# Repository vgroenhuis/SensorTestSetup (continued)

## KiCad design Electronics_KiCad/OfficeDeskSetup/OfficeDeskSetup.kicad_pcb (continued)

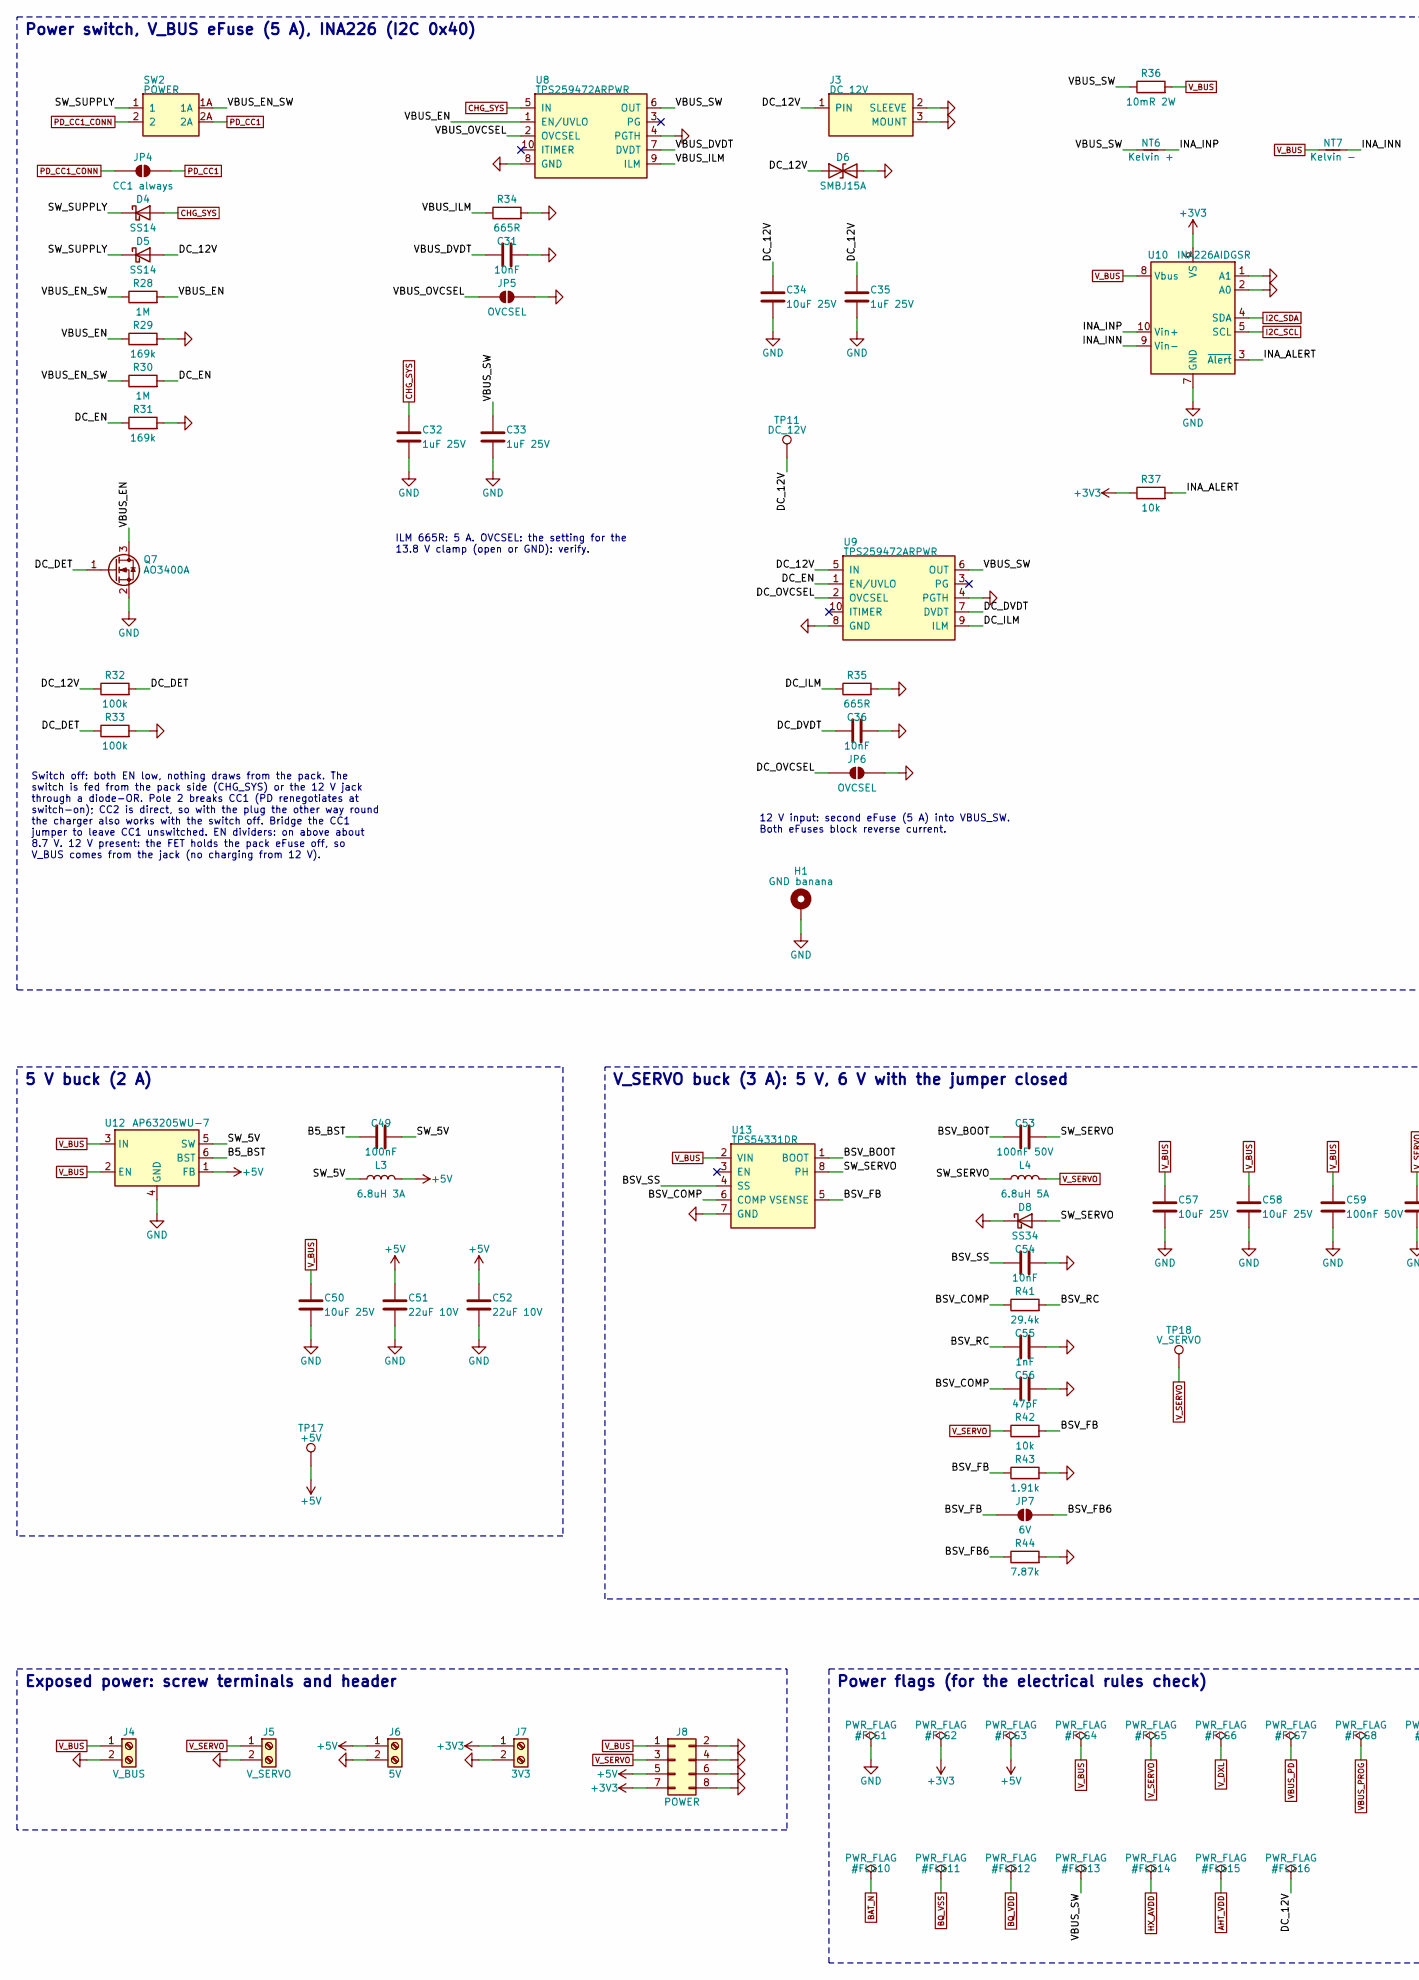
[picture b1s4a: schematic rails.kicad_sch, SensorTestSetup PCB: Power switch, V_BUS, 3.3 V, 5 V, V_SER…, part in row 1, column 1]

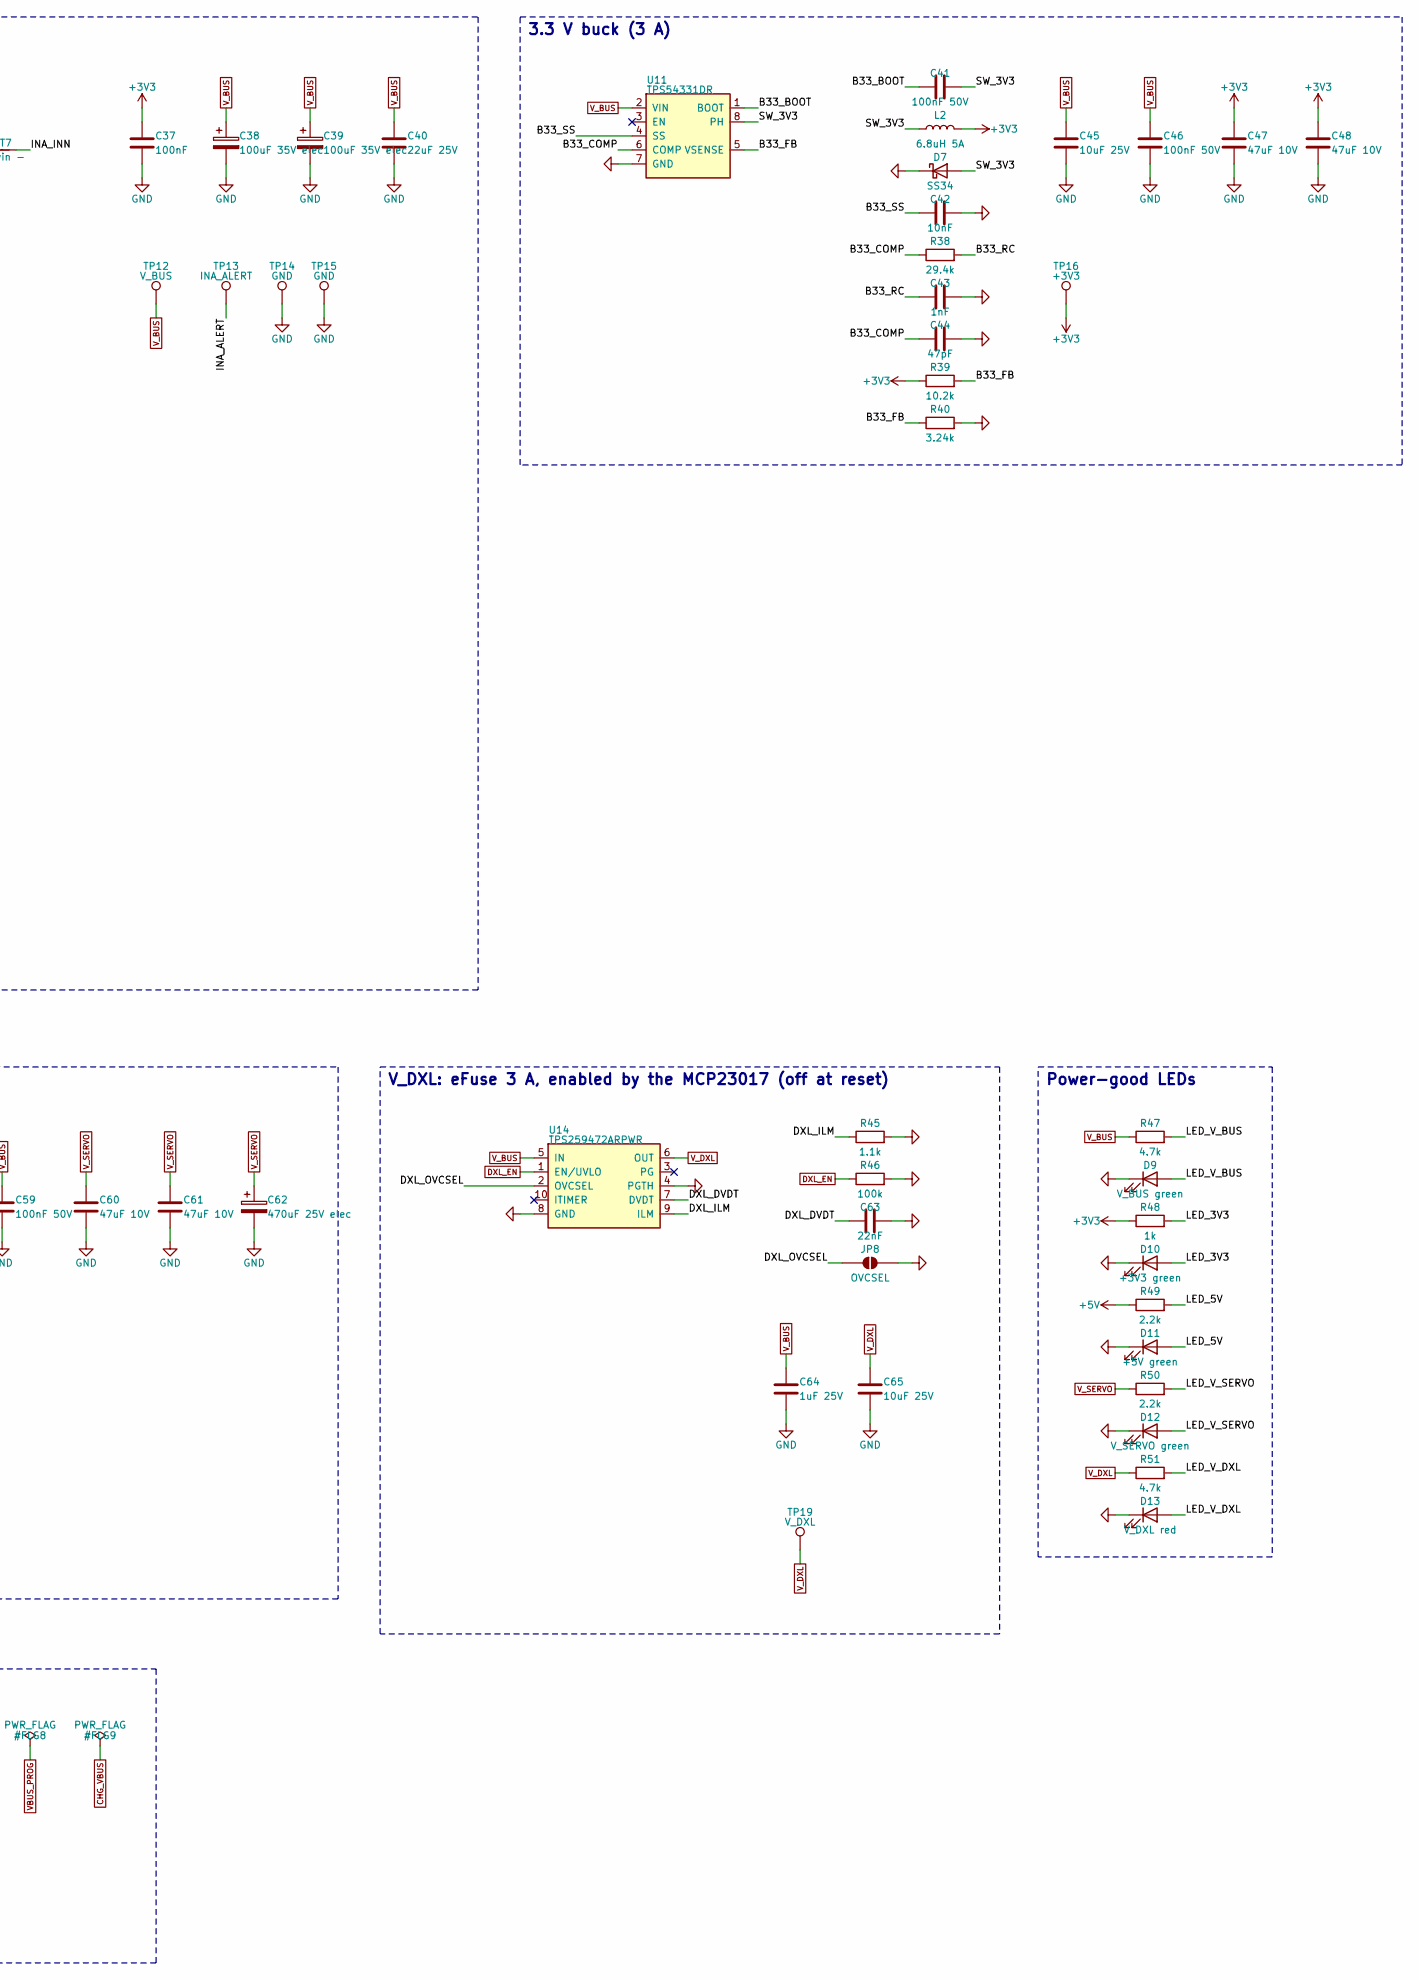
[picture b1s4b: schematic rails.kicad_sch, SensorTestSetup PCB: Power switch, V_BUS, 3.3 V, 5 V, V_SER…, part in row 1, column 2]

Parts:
C31, C36, C42, C54: 10nF; C_0603_1608Metric; LCSC C57112
C32, C33, C35, C64: 1uF 25V; C_0603_1608Metric; LCSC C15849
C34, C45, C50, C57, C58, C65: 10uF 25V; C_1206_3216Metric; LCSC C13585
C37, C49: 100nF; C_0603_1608Metric; LCSC C14663
C38, C39: 100uF 35V elec; CP_Elec_8x10; LCSC C2895269
C40: 22uF 25V; C_1206_3216Metric; LCSC C12891
C41, C46, C53, C59: 100nF 50V; C_0603_1608Metric; LCSC C14663
C43, C55: 1nF; C_0603_1608Metric; LCSC C1588
C44, C56: 47pF; C_0603_1608Metric; LCSC C1671
C47, C48, C60, C61: 47uF 10V; C_1206_3216Metric; LCSC C96123
C51, C52: 22uF 10V; C_1206_3216Metric; LCSC C12891
C62: 470uF 25V elec; CP_Elec_10x10; LCSC C3445246
C63: 22nF; C_0603_1608Metric; LCSC C21122
D4, D5: SS14; D_SMA; LCSC C2480
D6: SMBJ15A; D_SMB; LCSC C435932
D7, D8: SS34; D_SMA; LCSC C8678
D9: V_BUS green; LED_0603_1608Metric; LCSC C12624
D10: +3V3 green; LED_0603_1608Metric; LCSC C12624
D11: +5V green; LED_0603_1608Metric; LCSC C12624
D12: V_SERVO green; LED_0603_1608Metric; LCSC C12624
D13: V_DXL red; LED_0603_1608Metric; LCSC C2286
H1: GND banana; BananaHole_4.1mm_Pad
J3: DC 12V; DC-IN-TH_HX-DC007B-2.5; LCSC C17701683
J4: V_BUS; TerminalBlock_Phoenix_MKDS-1,5-2-5.08_1x02_P5.08mm_Horizont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; LCSC C8465
J5: V_SERVO; TerminalBlock_Phoenix_MKDS-1,5-2-5.08_1x02_P5.08mm_Horizont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; LCSC C8465
J6: 5V; TerminalBlock_Phoenix_MKDS-1,5-2-5.08_1x02_P5.08mm_Horizont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; LCSC C8465
J7: 3V3; TerminalBlock_Phoenix_MKDS-1,5-2-5.08_1x02_P5.08mm_Horizont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; LCSC C8465
J8: POWER; PinHeader_2x04_P2.54mm_Vertical; LCSC C32713277
JP4: CC1 always; SolderJumper-2_P1.3mm_Open_RoundedPad1.0x1.5mm
JP5, JP6, JP8: OVCSEL; SolderJumper-2_P1.3mm_Open_RoundedPad1.0x1.5mm
JP7: 6V; SolderJumper-2_P1.3mm_Open_RoundedPad1.0x1.5mm
L2, L4: 6.8uH 5A; IND-SMD_L7.0-W6.6; LCSC C167221
L3: 6.8uH 3A; IND-SMD_L7.0-W6.6; LCSC C167221
NT6: Kelvin +; NetTie-2_SMD_Pad0.5mm
NT7: Kelvin -; NetTie-2_SMD_Pad0.5mm
Q7: AO3400A; SOT-23; LCSC C20917
R28, R30: 1M; R_0603_1608Metric; LCSC C22935
R29, R31: 169k; R_0603_1608Metric; LCSC C22817
R32, R33, R46: 100k; R_0603_1608Metric; LCSC C25803
R34, R35: 665R; R_0603_1608Metric; LCSC C218112
R36: 10mR 2W; R_2512_6332Metric; LCSC C192580
R37, R42: 10k; R_0603_1608Metric; LCSC C25804
R38, R41: 29.4k; R_0603_1608Metric; LCSC C22974
R39: 10.2k; R_0603_1608Metric; LCSC C22772
R40: 3.24k; R_0603_1608Metric; LCSC C22994
R43: 1.91k; R_0603_1608Metric; LCSC C22853
R44: 7.87k; R_0603_1608Metric; LCSC C23236
R45: 1.1k; R_0603_1608Metric; LCSC C22764
R47, R51: 4.7k; R_0603_1608Metric; LCSC C23162
R48: 1k; R_0603_1608Metric; LCSC C21190
R49, R50: 2.2k; R_0603_1608Metric; LCSC C4190
SW2: POWER; SW-TH_SS21-BBIWG2-B; LCSC C6775929
TP11: DC_12V; TestPoint_Pad_D1.5mm
TP12: V_BUS; TestPoint_Pad_D1.5mm
TP13: INA_ALERT; TestPoint_Pad_D1.5mm
TP14, TP15: GND; TestPoint_Pad_D1.5mm
TP16: +3V3; TestPoint_Pad_D1.5mm
TP17: +5V; TestPoint_Pad_D1.5mm
TP18: V_SERVO; TestPoint_Pad_D1.5mm
TP19: V_DXL; TestPoint_Pad_D1.5mm
U8, U9, U14: TPS259472ARPWR; VQFN-10_L2.0-W2.0-P0.45-TL; LCSC C3662789
U10: INA226AIDGSR; TSSOP-10_3x3mm_P0.5mm; LCSC C49851
U11, U13: TPS54331DR; SOIC-8_3.9x4.9mm_P1.27mm; LCSC C9865
U12: AP63205WU-7; TSOT-23-6; LCSC C2071056

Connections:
+3V3: C37.1, C47.1, C48.1, J7.1, J8.7, L2.2, R37.1, R39.1, R48.1, TP16.1, U10.6 (VS); also elsewhere on the board
+5V: C51.1, C52.1, J6.1, J8.5, L3.2, R49.1, TP17.1, U12.1 (FB); also elsewhere on the board
/3 Power switch, V_BUS, 3.3 V, 5 V, V_SERVO, V_DXL/B5_BST: C49.1, U12.6 (BST)
/3 Power switch, V_BUS, 3.3 V, 5 V, V_SERVO, V_DXL/B33_BOOT: C41.1, U11.1 (BOOT)
/3 Power switch, V_BUS, 3.3 V, 5 V, V_SERVO, V_DXL/B33_COMP: C44.1, R38.1, U11.6 (COMP)
/3 Power switch, V_BUS, 3.3 V, 5 V, V_SERVO, V_DXL/B33_FB: R39.2, R40.1, U11.5 (VSENSE)
/3 Power switch, V_BUS, 3.3 V, 5 V, V_SERVO, V_DXL/B33_RC: C43.1, R38.2
/3 Power switch, V_BUS, 3.3 V, 5 V, V_SERVO, V_DXL/B33_SS: C42.1, U11.4 (SS)
/3 Power switch, V_BUS, 3.3 V, 5 V, V_SERVO, V_DXL/BSV_BOOT: C53.1, U13.1 (BOOT)
/3 Power switch, V_BUS, 3.3 V, 5 V, V_SERVO, V_DXL/BSV_COMP: C56.1, R41.1, U13.6 (COMP)
/3 Power switch, V_BUS, 3.3 V, 5 V, V_SERVO, V_DXL/BSV_FB: JP7.1 (A), R42.2, R43.1, U13.5 (VSENSE)
/3 Power switch, V_BUS, 3.3 V, 5 V, V_SERVO, V_DXL/BSV_FB6: JP7.2 (B), R44.1
/3 Power switch, V_BUS, 3.3 V, 5 V, V_SERVO, V_DXL/BSV_RC: C55.1, R41.2
/3 Power switch, V_BUS, 3.3 V, 5 V, V_SERVO, V_DXL/BSV_SS: C54.1, U13.4 (SS)
/3 Power switch, V_BUS, 3.3 V, 5 V, V_SERVO, V_DXL/DC_12V: C34.1, C35.1, D5.2 (A), D6.1 (A1), J3.1 (PIN), R32.1, TP11.1, U9.5 (IN)
/3 Power switch, V_BUS, 3.3 V, 5 V, V_SERVO, V_DXL/DC_DET: Q7.1 (G), R32.2, R33.1
/3 Power switch, V_BUS, 3.3 V, 5 V, V_SERVO, V_DXL/DC_DVDT: C36.1, U9.7 (DVDT)
/3 Power switch, V_BUS, 3.3 V, 5 V, V_SERVO, V_DXL/DC_EN: R30.2, R31.1, U9.1 (EN/UVLO)
/3 Power switch, V_BUS, 3.3 V, 5 V, V_SERVO, V_DXL/DC_ILM: R35.1, U9.9 (ILM)
/3 Power switch, V_BUS, 3.3 V, 5 V, V_SERVO, V_DXL/DC_OVCSEL: JP6.1 (A), U9.2 (OVCSEL)
/3 Power switch, V_BUS, 3.3 V, 5 V, V_SERVO, V_DXL/DXL_DVDT: C63.1, U14.7 (DVDT)
/3 Power switch, V_BUS, 3.3 V, 5 V, V_SERVO, V_DXL/DXL_ILM: R45.1, U14.9 (ILM)
/3 Power switch, V_BUS, 3.3 V, 5 V, V_SERVO, V_DXL/DXL_OVCSEL: JP8.1 (A), U14.2 (OVCSEL)
/3 Power switch, V_BUS, 3.3 V, 5 V, V_SERVO, V_DXL/INA_ALERT: R37.2, TP13.1, U10.3 (~Alert)
/3 Power switch, V_BUS, 3.3 V, 5 V, V_SERVO, V_DXL/INA_INN: NT7.2, U10.9 (Vin-)
/3 Power switch, V_BUS, 3.3 V, 5 V, V_SERVO, V_DXL/INA_INP: NT6.2, U10.10 (Vin+)
/3 Power switch, V_BUS, 3.3 V, 5 V, V_SERVO, V_DXL/LED_3V3: D10.2 (A), R48.2
/3 Power switch, V_BUS, 3.3 V, 5 V, V_SERVO, V_DXL/LED_5V: D11.2 (A), R49.2
/3 Power switch, V_BUS, 3.3 V, 5 V, V_SERVO, V_DXL/LED_V_BUS: D9.2 (A), R47.2
/3 Power switch, V_BUS, 3.3 V, 5 V, V_SERVO, V_DXL/LED_V_DXL: D13.2 (A), R51.2
/3 Power switch, V_BUS, 3.3 V, 5 V, V_SERVO, V_DXL/LED_V_SERVO: D12.2 (A), R50.2
/3 Power switch, V_BUS, 3.3 V, 5 V, V_SERVO, V_DXL/SW_3V3: C41.2, D7.2 (A), L2.1, U11.8 (PH)
/3 Power switch, V_BUS, 3.3 V, 5 V, V_SERVO, V_DXL/SW_5V: C49.2, L3.1, U12.5 (SW)
/3 Power switch, V_BUS, 3.3 V, 5 V, V_SERVO, V_DXL/SW_SERVO: C53.2, D8.2 (A), L4.1, U13.8 (PH)
/3 Power switch, V_BUS, 3.3 V, 5 V, V_SERVO, V_DXL/SW_SUPPLY: D4.1 (K), D5.1 (K), SW2.1
/3 Power switch, V_BUS, 3.3 V, 5 V, V_SERVO, V_DXL/VBUS_DVDT: C31.1, U8.7 (DVDT)
/3 Power switch, V_BUS, 3.3 V, 5 V, V_SERVO, V_DXL/VBUS_EN: Q7.3 (D), R28.2, R29.1, U8.1 (EN/UVLO)
/3 Power switch, V_BUS, 3.3 V, 5 V, V_SERVO, V_DXL/VBUS_EN_SW: R28.1, R30.1, SW2.1A
/3 Power switch, V_BUS, 3.3 V, 5 V, V_SERVO, V_DXL/VBUS_ILM: R34.1, U8.9 (ILM)
/3 Power switch, V_BUS, 3.3 V, 5 V, V_SERVO, V_DXL/VBUS_OVCSEL: JP5.1 (A), U8.2 (OVCSEL)
/3 Power switch, V_BUS, 3.3 V, 5 V, V_SERVO, V_DXL/VBUS_SW: C33.1, NT6.1, R36.1, U8.6 (OUT), U9.6 (OUT)
CHG_SYS: C32.1, D4.2 (A), U8.5 (IN); also elsewhere on the board
DXL_EN: R46.1, U14.1 (EN/UVLO); also elsewhere on the board
GND: C31.2, C32.2, C33.2, C34.2, C35.2, C36.2, C37.2, C38.2, C39.2, C40.2, C42.2, C43.2, C44.2, C45.2, C46.2, C47.2, C48.2, C50.2, C51.2, C52.2, C54.2, C55.2, C56.2, C57.2, C58.2, C59.2, C60.2, C61.2, C62.2, C63.2, C64.2, C65.2, D6.2 (A2), D7.1 (K), D8.1 (K), D9.1 (K), D10.1 (K), D11.1 (K), D12.1 (K), D13.1 (K), H1.1, J3.2 (SLEEVE), J3.3 (MOUNT), J4.2, J5.2, J6.2, J7.2, J8.2, J8.4, J8.6, J8.8, JP5.2 (B), JP6.2 (B), JP8.2 (B), Q7.2 (S), R29.2, R31.2, R33.2, R34.2, R35.2, R40.2, R43.2, R44.2, R45.2, R46.2, TP14.1, TP15.1, U8.4 (PGTH), U8.8 (GND), U9.4 (PGTH), U9.8 (GND), U10.1 (A1), U10.2 (A0), U10.7 (GND), U11.7 (GND), U12.4 (GND), U13.7 (GND), U14.4 (PGTH), U14.8 (GND); also elsewhere on the board
I2C_SCL: U10.5 (SCL); also elsewhere on the board
I2C_SDA: U10.4 (SDA); also elsewhere on the board
PD_CC1: JP4.2 (B), SW2.2A; also elsewhere on the board
PD_CC1_CONN: JP4.1 (A), SW2.2; also elsewhere on the board
V_BUS: C38.1, C39.1, C40.1, C45.1, C46.1, C50.1, C57.1, C58.1, C59.1, C64.1, J4.1, J8.1, NT7.1, R36.2, R47.1, TP12.1, U10.8 (Vbus), U11.2 (VIN), U12.2 (EN), U12.3 (IN), U13.2 (VIN), U14.5 (IN); also elsewhere on the board
V_DXL: C65.1, R51.1, TP19.1, U14.6 (OUT); also elsewhere on the board
V_SERVO: C60.1, C61.1, C62.1, J5.1, J8.3, L4.2, R42.1, R50.1, TP18.1; also elsewhere on the board

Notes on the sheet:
Switch off: both EN low, nothing draws from the pack. The switch is fed from the pack side (CHG_SYS) or the 12 V jack through a diode-OR. Pole 2 breaks CC1 (PD renegotiates at switch-on); CC2 is direct, so with the plug the other way round the charger also works with the switch off. Bridge the CC1 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
ILM 665R: 5 A. OVCSEL: the setting for the 13.8 V clamp (open or GND): verify.
12 V input: second eFuse (5 A) into VBUS_SW. Both eFuses block reverse current.
Power switch, V_BUS eFuse (5 A), INA226 (I2C 0x40)
3.3 V buck (3 A)
5 V buck (2 A)
V_SERVO buck (3 A): 5 V, 6 V with the jumper closed
V_DXL: eFuse 3 A, enabled by the MCP23017 (off at reset)
Power-good LEDs
Exposed power: screw terminals and header
Power flags (for the electrical rules check)

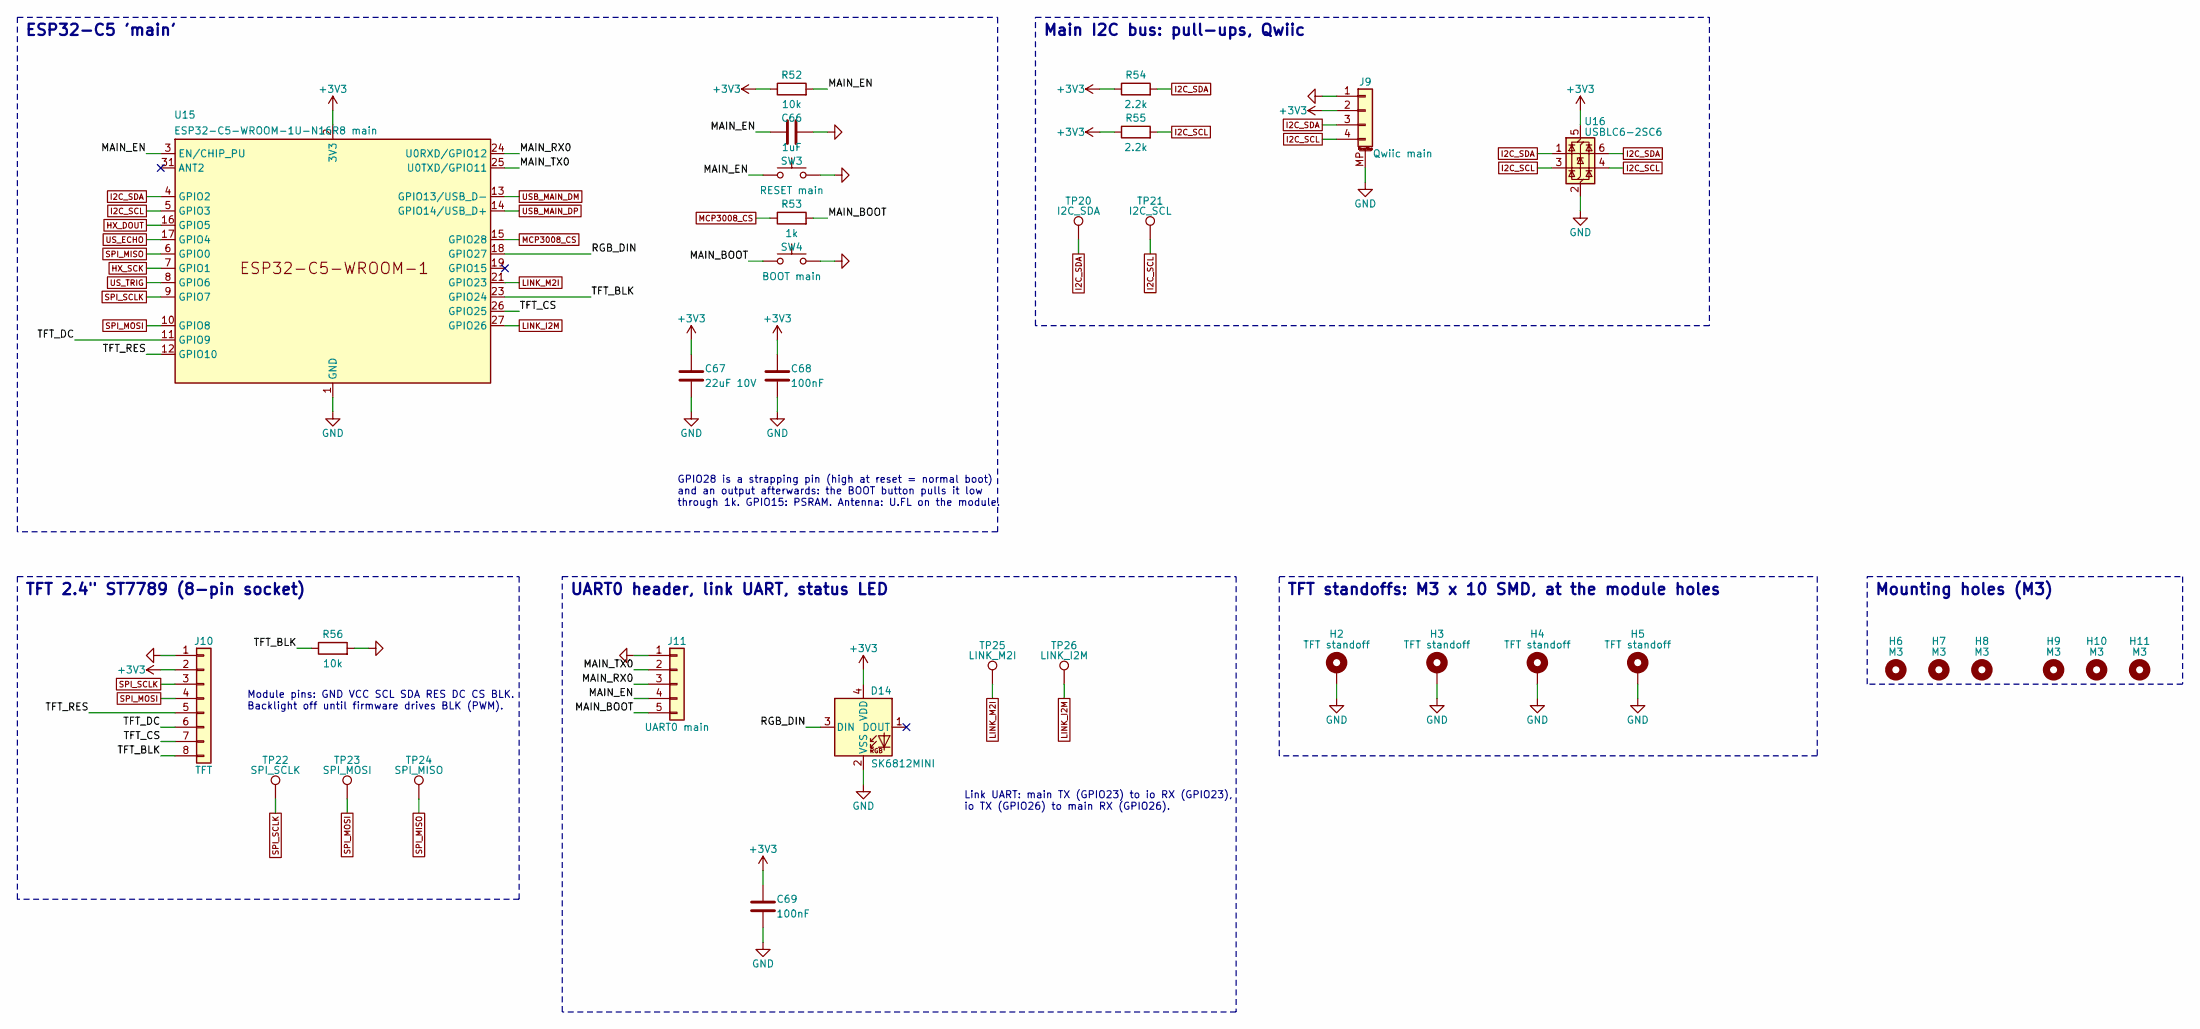
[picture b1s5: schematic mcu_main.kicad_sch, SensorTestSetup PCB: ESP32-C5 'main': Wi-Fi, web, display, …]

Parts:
C66: 1uF; C_0603_1608Metric; LCSC C15849
C67: 22uF 10V; C_1206_3216Metric; LCSC C12891
C68, C69: 100nF; C_0603_1608Metric; LCSC C14663
D14: SK6812MINI; LED_SK6812MINI_PLCC4_3.5x3.5mm_P1.75mm; LCSC C5183448
H2, H3, H4, H5: TFT standoff; SCREW-SMD_BD5.6-D4.1-H10; LCSC C2916370
H6, H7, H8, H9, H10, H11: M3; MountingHole_3.2mm_M3
J9: Qwiic main; JST_SH_SM04B-SRSS-TB_1x04-1MP_P1.00mm_Horizontal; LCSC C51940130
J10: TFT; PinSocket_1x08_P2.54mm_Vertical; LCSC C27438
J11: UART0 main; PinHeader_1x05_P2.54mm_Vertical; LCSC C32713271
R52, R56: 10k; R_0603_1608Metric; LCSC C25804
R53: 1k; R_0603_1608Metric; LCSC C21190
R54, R55: 2.2k; R_0603_1608Metric; LCSC C4190
SW3: RESET main; SW-SMD_4P-L5.1-W5.1-P3.70-LS6.5-TL_H1.5; LCSC C318884
SW4: BOOT main; SW-SMD_4P-L5.1-W5.1-P3.70-LS6.5-TL_H1.5; LCSC C318884
TP20: I2C_SDA; TestPoint_Pad_D1.5mm
TP21: I2C_SCL; TestPoint_Pad_D1.5mm
TP22: SPI_SCLK; TestPoint_Pad_D1.5mm
TP23: SPI_MOSI; TestPoint_Pad_D1.5mm
TP24: SPI_MISO; TestPoint_Pad_D1.5mm
TP25: LINK_M2I; TestPoint_Pad_D1.5mm
TP26: LINK_I2M; TestPoint_Pad_D1.5mm
U15: ESP32-C5-WROOM-1U-N16R8 main; ESP32-C5-WROOM-1U; LCSC C54951857
U16: USBLC6-2SC6; SOT-23-6; LCSC C2827654

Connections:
+3V3: C67.1, C68.1, C69.1, D14.4 (VDD), J9.2, J10.2, R52.1, R54.1, R55.1, U15.2 (3V3), U16.5 (VBUS); also elsewhere on the board
/4 ESP32-C5 'main': Wi-Fi, web, display, SPI, main I2C bus/MAIN_BOOT: J11.5, R53.2, SW4.1
/4 ESP32-C5 'main': Wi-Fi, web, display, SPI, main I2C bus/MAIN_EN: C66.1, J11.4, R52.2, SW3.1, U15.3 (EN/CHIP_PU)
/4 ESP32-C5 'main': Wi-Fi, web, display, SPI, main I2C bus/MAIN_RX0: J11.3, U15.24 (U0RXD/GPIO12)
/4 ESP32-C5 'main': Wi-Fi, web, display, SPI, main I2C bus/MAIN_TX0: J11.2, U15.25 (U0TXD/GPIO11)
/4 ESP32-C5 'main': Wi-Fi, web, display, SPI, main I2C bus/RGB_DIN: D14.3 (DIN), U15.18 (GPIO27)
/4 ESP32-C5 'main': Wi-Fi, web, display, SPI, main I2C bus/TFT_BLK: J10.8, R56.1, U15.23 (GPIO24)
/4 ESP32-C5 'main': Wi-Fi, web, display, SPI, main I2C bus/TFT_CS: J10.7, U15.26 (GPIO25)
/4 ESP32-C5 'main': Wi-Fi, web, display, SPI, main I2C bus/TFT_DC: J10.6, U15.11 (GPIO9)
/4 ESP32-C5 'main': Wi-Fi, web, display, SPI, main I2C bus/TFT_RES: J10.5, U15.12 (GPIO10)
GND: C66.2, C67.2, C68.2, C69.2, D14.2 (VSS), H2.1, H3.1, H4.1, H5.1, J9.1, J9.MP (MountPin), J10.1, J11.1, R56.2, SW3.2, SW4.2, U15.1 (GND), U15.28 (GND), U15.29 (GND), U15.30 (GND), U15.32 (GND), U16.2 (GND); also elsewhere on the board
HX_DOUT: U15.16 (GPIO5); also elsewhere on the board
HX_SCK: U15.7 (GPIO1); also elsewhere on the board
I2C_SCL: J9.4, R55.2, TP21.1, U15.5 (GPIO3), U16.3 (I/O2), U16.4 (I/O2); also elsewhere on the board
I2C_SDA: J9.3, R54.2, TP20.1, U15.4 (GPIO2), U16.1 (I/O1), U16.6 (I/O1); also elsewhere on the board
LINK_I2M: TP26.1, U15.27 (GPIO26); also elsewhere on the board
LINK_M2I: TP25.1, U15.21 (GPIO23); also elsewhere on the board
MCP3008_CS: R53.1, U15.15 (GPIO28); also elsewhere on the board
SPI_MISO: TP24.1, U15.6 (GPIO0); also elsewhere on the board
SPI_MOSI: J10.4, TP23.1, U15.10 (GPIO8); also elsewhere on the board
SPI_SCLK: J10.3, TP22.1, U15.9 (GPIO7); also elsewhere on the board
USB_MAIN_DM: U15.13 (GPIO13/USB_D-); also elsewhere on the board
USB_MAIN_DP: U15.14 (GPIO14/USB_D+); also elsewhere on the board
US_ECHO: U15.17 (GPIO4); also elsewhere on the board
US_TRIG: U15.8 (GPIO6); also elsewhere on the board

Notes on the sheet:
GPIO28 is a strapping pin (high at reset = normal boot) and an output afterwards: the BOOT button pulls it low through 1k. GPIO15: PSRAM. Antenna: U.FL on the module.
ESP32-C5 'main'
Main I2C bus: pull-ups, Qwiic
Module pins: GND VCC SCL SDA RES DC CS BLK. Backlight off until firmware drives BLK (PWM).
TFT 2.4" ST7789 (8-pin socket)
Link UART: main TX (GPIO23) to io RX (GPIO23), io TX (GPIO26) to main RX (GPIO26).
UART0 header, link UART, status LED
TFT standoffs: M3 x 10 SMD, at the module holes
Mounting holes (M3)

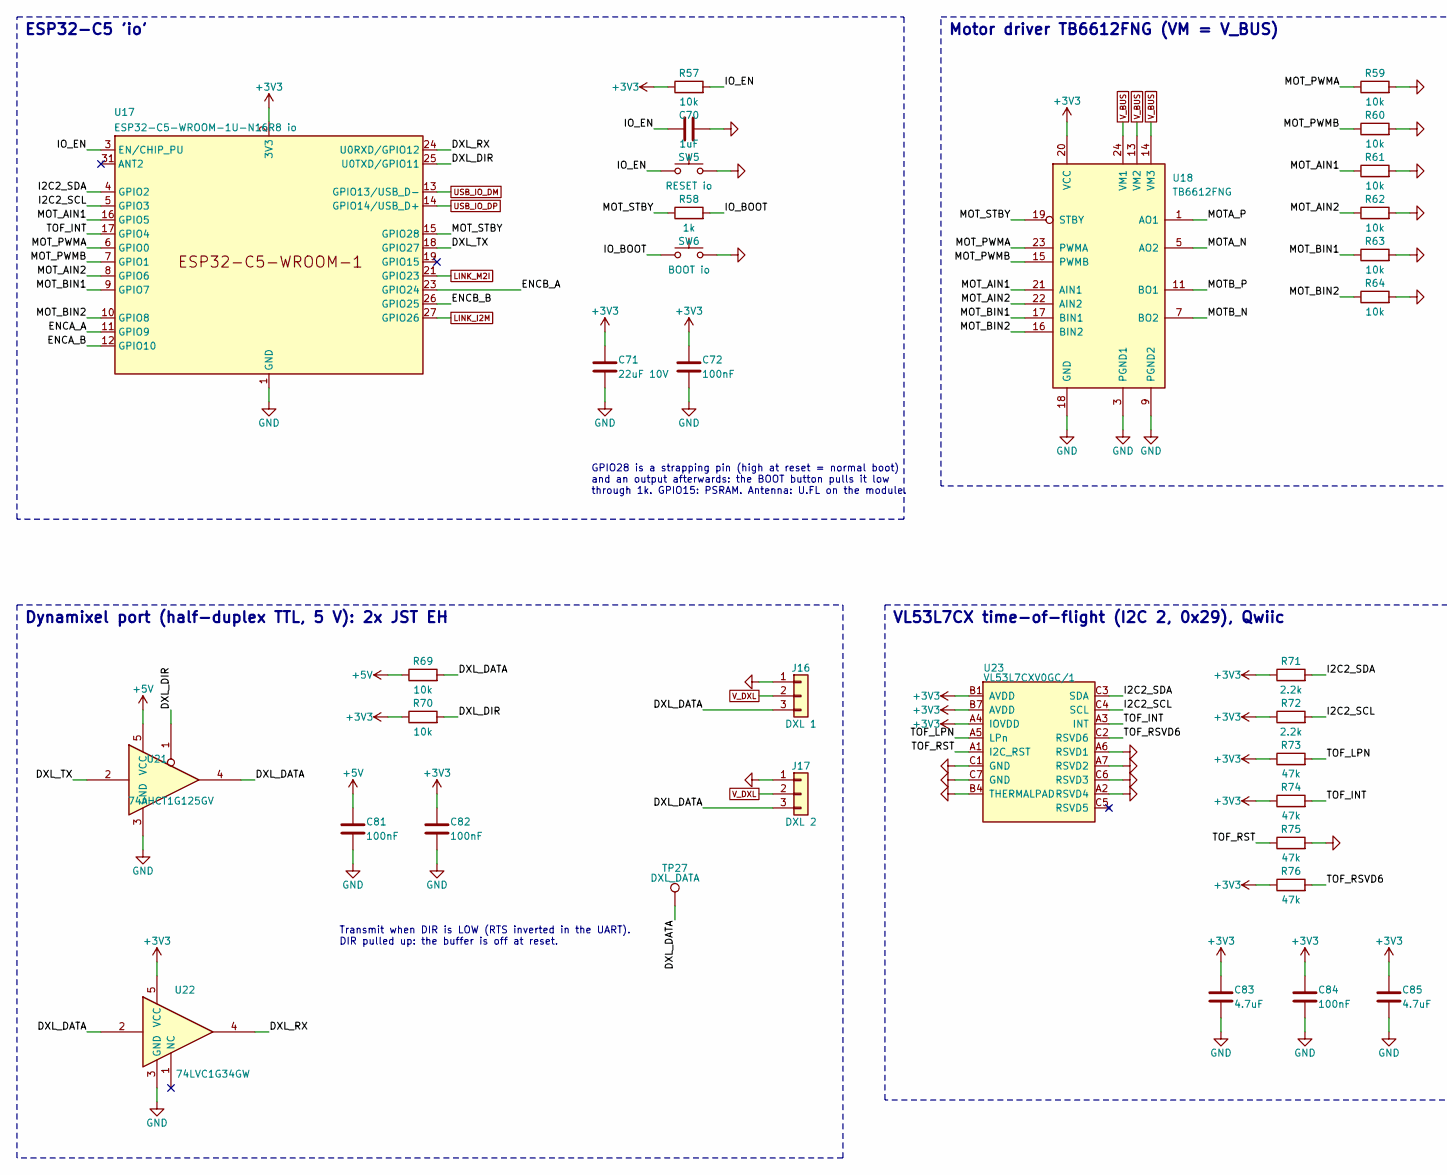
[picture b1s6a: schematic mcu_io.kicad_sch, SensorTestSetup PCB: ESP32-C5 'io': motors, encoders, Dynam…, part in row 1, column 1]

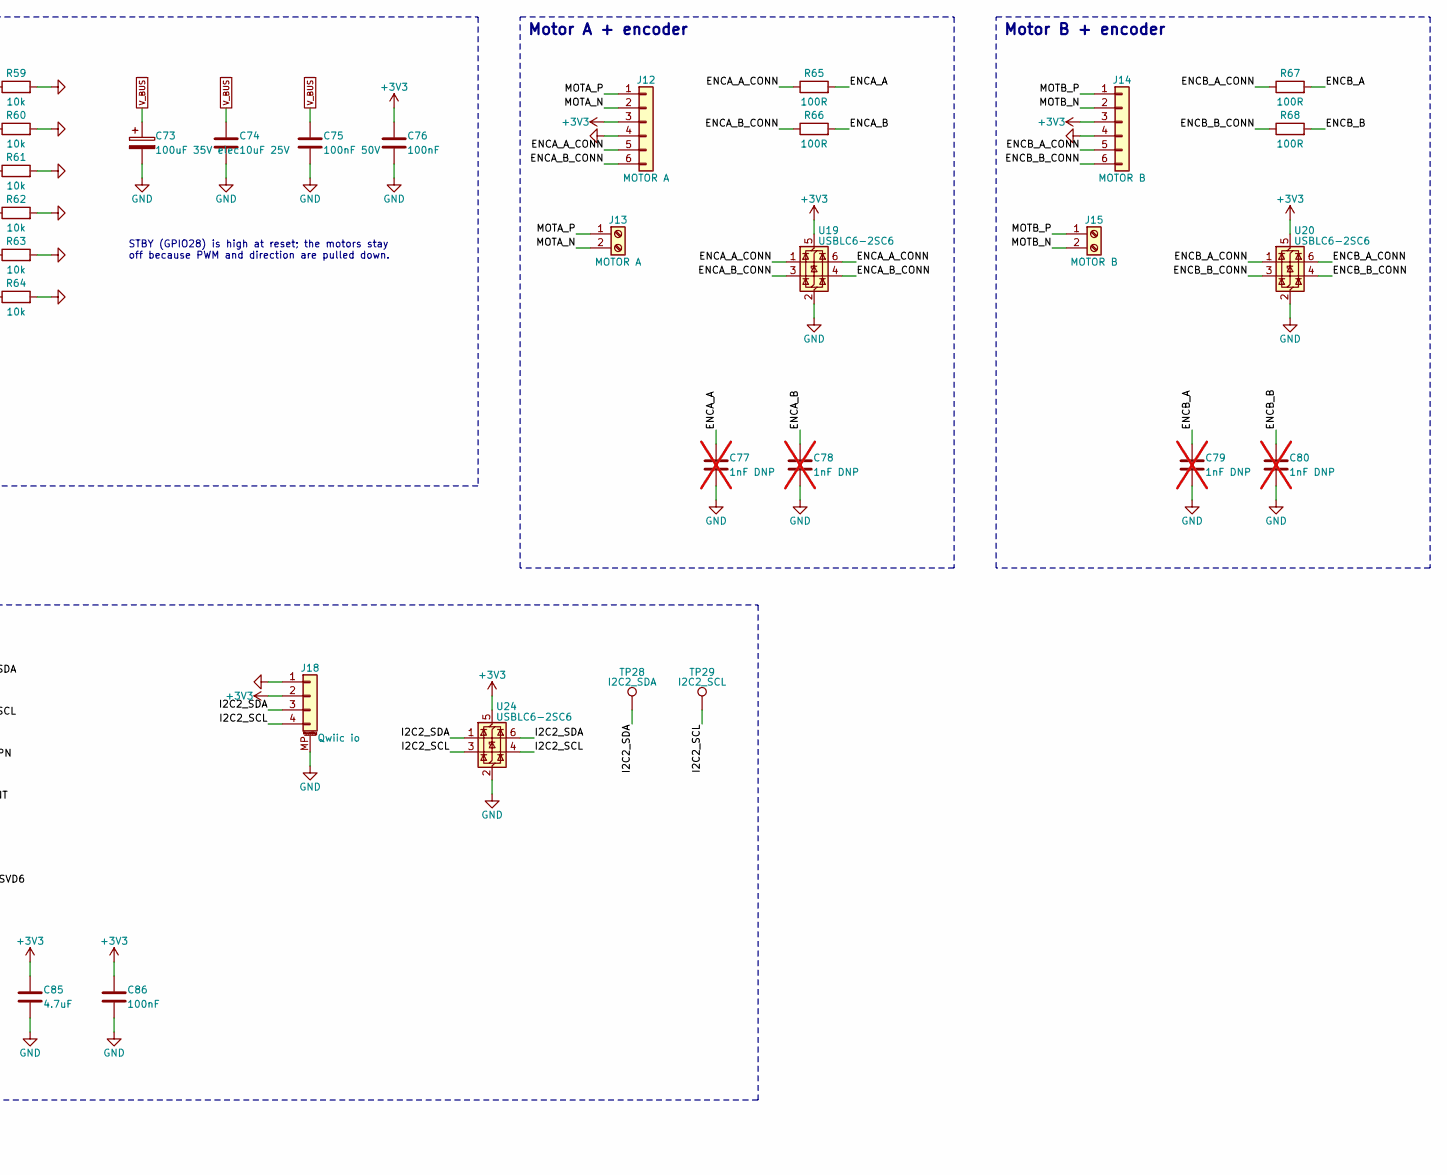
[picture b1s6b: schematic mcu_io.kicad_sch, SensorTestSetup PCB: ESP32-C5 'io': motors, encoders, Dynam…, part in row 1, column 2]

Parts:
C70: 1uF; C_0603_1608Metric; LCSC C15849
C71: 22uF 10V; C_1206_3216Metric; LCSC C12891
C72, C76, C81, C82, C84, C86: 100nF; C_0603_1608Metric; LCSC C14663
C73: 100uF 35V elec; CP_Elec_8x10; LCSC C2895269
C74: 10uF 25V; C_1206_3216Metric; LCSC C13585
C75: 100nF 50V; C_0603_1608Metric; LCSC C14663
C77, C78, C79, C80: 1nF DNP; C_0603_1608Metric; LCSC C1588; not fitted
C83, C85: 4.7uF; C_0805_2012Metric; LCSC C1779
J12: MOTOR A; JST_PH_B6B-PH-K_1x06_P2.00mm_Vertical; LCSC C131342
J13: MOTOR A; TerminalBlock_Phoenix_MKDS-1,5-2-5.08_1x02_P5.08mm_Horizont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; LCSC C8465
J14: MOTOR B; JST_PH_B6B-PH-K_1x06_P2.00mm_Vertical; LCSC C131342
J15: MOTOR B; TerminalBlock_Phoenix_MKDS-1,5-2-5.08_1x02_P5.08mm_Horizont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; LCSC C8465
J16: DXL 1; JST_EH_B3B-EH-A_1x03_P2.50mm_Vertical; LCSC C160259
J17: DXL 2; JST_EH_B3B-EH-A_1x03_P2.50mm_Vertical; LCSC C160259
J18: Qwiic io; JST_SH_SM04B-SRSS-TB_1x04-1MP_P1.00mm_Horizontal; LCSC C51940130
R57, R59, R60, R61, R62, R63, R64, R69, R70: 10k; R_0603_1608Metric; LCSC C25804
R58: 1k; R_0603_1608Metric; LCSC C21190
R65, R66, R67, R68: 100R; R_0603_1608Metric; LCSC C22775
R71, R72: 2.2k; R_0603_1608Metric; LCSC C4190
R73, R74, R75, R76: 47k; R_0603_1608Metric; LCSC C25819
SW5: RESET io; SW-SMD_4P-L5.1-W5.1-P3.70-LS6.5-TL_H1.5; LCSC C318884
SW6: BOOT io; SW-SMD_4P-L5.1-W5.1-P3.70-LS6.5-TL_H1.5; LCSC C318884
TP27: DXL_DATA; TestPoint_Pad_D1.5mm
TP28: I2C2_SDA; TestPoint_Pad_D1.5mm
TP29: I2C2_SCL; TestPoint_Pad_D1.5mm
U17: ESP32-C5-WROOM-1U-N16R8 io; ESP32-C5-WROOM-1U; LCSC C54951857
U18: TB6612FNG; SSOP-24_5.3x8.2mm_P0.65mm; LCSC C141517
U19, U20, U24: USBLC6-2SC6; SOT-23-6; LCSC C2827654
U21: 74AHCT1G125GV; SOT-23-5; LCSC C52140417
U22: 74LVC1G34GW; SOT-353_SC-70-5; LCSC C52140426
U23: VL53L7CXV0GC/1; LGA-16_L6.4-W3.0_VL53L5CXV0GC-1; LCSC C5270520

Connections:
+3V3: C71.1, C72.1, C76.1, C82.1, C83.1, C84.1, C85.1, C86.1, J12.3, J14.3, J18.2, R57.1, R70.1, R71.1, R72.1, R73.1, R74.1, R76.1, U17.2 (3V3), U18.20 (VCC), U19.5 (VBUS), U20.5 (VBUS), U22.5 (VCC), U23.A4 (IOVDD), U23.B1 (AVDD), U23.B7 (AVDD), U24.5 (VBUS); also elsewhere on the board
+5V: C81.1, R69.1, U21.5 (VCC); also elsewhere on the board
/5 ESP32-C5 'io': motors, encoders, Dynamixel, ToF/DXL_DATA: J16.3, J17.3, R69.2, TP27.1, U21.4, U22.2
/5 ESP32-C5 'io': motors, encoders, Dynamixel, ToF/DXL_DIR: R70.2, U17.25 (U0TXD/GPIO11), U21.1
/5 ESP32-C5 'io': motors, encoders, Dynamixel, ToF/DXL_RX: U17.24 (U0RXD/GPIO12), U22.4
/5 ESP32-C5 'io': motors, encoders, Dynamixel, ToF/DXL_TX: U17.18 (GPIO27), U21.2
/5 ESP32-C5 'io': motors, encoders, Dynamixel, ToF/ENCA_A: C77.1, R65.2, U17.11 (GPIO9)
/5 ESP32-C5 'io': motors, encoders, Dynamixel, ToF/ENCA_A_CONN: J12.5, R65.1, U19.1 (I/O1), U19.6 (I/O1)
/5 ESP32-C5 'io': motors, encoders, Dynamixel, ToF/ENCA_B: C78.1, R66.2, U17.12 (GPIO10)
/5 ESP32-C5 'io': motors, encoders, Dynamixel, ToF/ENCA_B_CONN: J12.6, R66.1, U19.3 (I/O2), U19.4 (I/O2)
/5 ESP32-C5 'io': motors, encoders, Dynamixel, ToF/ENCB_A: C79.1, R67.2, U17.23 (GPIO24)
/5 ESP32-C5 'io': motors, encoders, Dynamixel, ToF/ENCB_A_CONN: J14.5, R67.1, U20.1 (I/O1), U20.6 (I/O1)
/5 ESP32-C5 'io': motors, encoders, Dynamixel, ToF/ENCB_B: C80.1, R68.2, U17.26 (GPIO25)
/5 ESP32-C5 'io': motors, encoders, Dynamixel, ToF/ENCB_B_CONN: J14.6, R68.1, U20.3 (I/O2), U20.4 (I/O2)
/5 ESP32-C5 'io': motors, encoders, Dynamixel, ToF/I2C2_SCL: J18.4, R72.2, TP29.1, U17.5 (GPIO3), U23.C4 (SCL), U24.3 (I/O2), U24.4 (I/O2)
/5 ESP32-C5 'io': motors, encoders, Dynamixel, ToF/I2C2_SDA: J18.3, R71.2, TP28.1, U17.4 (GPIO2), U23.C3 (SDA), U24.1 (I/O1), U24.6 (I/O1)
/5 ESP32-C5 'io': motors, encoders, Dynamixel, ToF/IO_BOOT: R58.2, SW6.1
/5 ESP32-C5 'io': motors, encoders, Dynamixel, ToF/IO_EN: C70.1, R57.2, SW5.1, U17.3 (EN/CHIP_PU)
/5 ESP32-C5 'io': motors, encoders, Dynamixel, ToF/MOTA_N: J12.2, J13.2, U18.5 (AO2), U18.6 (AO2)
/5 ESP32-C5 'io': motors, encoders, Dynamixel, ToF/MOTA_P: J12.1, J13.1, U18.1 (AO1), U18.2 (AO1)
/5 ESP32-C5 'io': motors, encoders, Dynamixel, ToF/MOTB_N: J14.2, J15.2, U18.7 (BO2), U18.8 (BO2)
/5 ESP32-C5 'io': motors, encoders, Dynamixel, ToF/MOTB_P: J14.1, J15.1, U18.11 (BO1), U18.12 (BO1)
/5 ESP32-C5 'io': motors, encoders, Dynamixel, ToF/MOT_AIN1: R61.1, U17.16 (GPIO5), U18.21 (AIN1)
/5 ESP32-C5 'io': motors, encoders, Dynamixel, ToF/MOT_AIN2: R62.1, U17.8 (GPIO6), U18.22 (AIN2)
/5 ESP32-C5 'io': motors, encoders, Dynamixel, ToF/MOT_BIN1: R63.1, U17.9 (GPIO7), U18.17 (BIN1)
/5 ESP32-C5 'io': motors, encoders, Dynamixel, ToF/MOT_BIN2: R64.1, U17.10 (GPIO8), U18.16 (BIN2)
/5 ESP32-C5 'io': motors, encoders, Dynamixel, ToF/MOT_PWMA: R59.1, U17.6 (GPIO0), U18.23 (PWMA)
/5 ESP32-C5 'io': motors, encoders, Dynamixel, ToF/MOT_PWMB: R60.1, U17.7 (GPIO1), U18.15 (PWMB)
/5 ESP32-C5 'io': motors, encoders, Dynamixel, ToF/MOT_STBY: R58.1, U17.15 (GPIO28), U18.19 (STBY)
/5 ESP32-C5 'io': motors, encoders, Dynamixel, ToF/TOF_INT: R74.2, U17.17 (GPIO4), U23.A3 (INT)
/5 ESP32-C5 'io': motors, encoders, Dynamixel, ToF/TOF_LPN: R73.2, U23.A5 (LPn)
/5 ESP32-C5 'io': motors, encoders, Dynamixel, ToF/TOF_RST: R75.1, U23.A1 (I2C_RST)
/5 ESP32-C5 'io': motors, encoders, Dynamixel, ToF/TOF_RSVD6: R76.2, U23.C2 (RSVD6)
GND: C70.2, C71.2, C72.2, C73.2, C74.2, C75.2, C76.2, C77.2, C78.2, C79.2, C80.2, C81.2, C82.2, C83.2, C84.2, C85.2, C86.2, J12.4, J14.4, J16.1, J17.1, J18.1, J18.MP (MountPin), R59.2, R60.2, R61.2, R62.2, R63.2, R64.2, R75.2, SW5.2, SW6.2, U17.1 (GND), U17.28 (GND), U17.29 (GND), U17.30 (GND), U17.32 (GND), U18.3 (PGND1), U18.4 (PGND1), U18.9 (PGND2), U18.10 (PGND2), U18.18 (GND), U19.2 (GND), U20.2 (GND), U21.3 (GND), U22.3 (GND), U23.A2 (RSVD4), U23.A6 (RSVD1), U23.A7 (RSVD2), U23.B4 (THERMALPAD), U23.C1 (GND), U23.C6 (RSVD3), U23.C7 (GND), U24.2 (GND); also elsewhere on the board
LINK_I2M: U17.27 (GPIO26); also elsewhere on the board
LINK_M2I: U17.21 (GPIO23); also elsewhere on the board
USB_IO_DM: U17.13 (GPIO13/USB_D-); also elsewhere on the board
USB_IO_DP: U17.14 (GPIO14/USB_D+); also elsewhere on the board
V_BUS: C73.1, C74.1, C75.1, U18.13 (VM2), U18.14 (VM3), U18.24 (VM1); also elsewhere on the board
V_DXL: J16.2, J17.2; also elsewhere on the board

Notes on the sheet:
GPIO28 is a strapping pin (high at reset = normal boot) and an output afterwards: the BOOT button pulls it low through 1k. GPIO15: PSRAM. Antenna: U.FL on the module.
ESP32-C5 'io'
STBY (GPIO28) is high at reset; the motors stay off because PWM and direction are pulled down.
Motor driver TB6612FNG (VM = V_BUS)
Motor A + encoder
Motor B + encoder
Transmit when DIR is LOW (RTS inverted in the UART). DIR pulled up: the buffer is off at reset.
Dynamixel port (half-duplex TTL, 5 V): 2x JST EH
VL53L7CX time-of-flight (I2C 2, 0x29), Qwiic
